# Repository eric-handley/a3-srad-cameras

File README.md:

# SRAD Cameras -  Operator's Manual

Please read the following document carefully as there are several important notes that could result in data loss or damage if ignored. After the rocket is recovered, please follow [Post-Flight Operations](#post-flight-operations).

Various tools for interacting with the camera boards have been provided in `./tools`. Each of these scripts can be passed `-h` as a flag to see the correct usage. Usage of these scripts is also detailed throughout this file. These scripts + this manual is largely written with the assumption that the user is on a reasonably mainstream Linux distro with common tools available. 

You will need a USB-C cable to pull files off of the camera (although the SD card should be imaged after flight as a precaution before doing this) and a USB<->UART adapter to send/receive camera commands/status.

Please send me a message if uncertain about anything or if issues arise!

## Table of Contents

- [Pre-Flight Checklist](#pre-flight-checklist)
    - [FPC Cable](#fpc-cable)
    - [Arducam Module](#arducam-module)
    - [SD Card](#sd-card)
    - [Operational Test](#operational-test)
    - [Before Launch](#before-launch)
- [Important Warnings & Info](#important-warnings--info)
- [Board Info](#board-info)
    - [Camera Status](#camera-status)
    - [Correct FPC Orientation](#correct-fpc-orientation)
    - [Arducam Ribbon connector](#arducam-ribbon-connector)
- [SD Card Operations](#sd-card-operations)
    - [SD Card Format](#sd-card-format)
- [Recovering Recordings](#recovering-recordings)
    - [Post-Flight Operations](#post-flight-operations)
    - [Pulling Recordings Directly](#pulling-recordings-directly)
- [Inspecting Recording Logs for Issues](#inspecting-recording-logs-for-issues)
    - [Common Errors & Causes](#common-errors--causes)
    - [`CAM2` Errata](#cam2-errata)

## Pre-Flight Checklist

This checklist is per-camera, e.g. each item should be checked on each camera module.

##### FPC Cable

- [ ] FPC is securely connected to both boards, without unneccesary strain, bends, or creases
- [ ] The FPC cable is oriented correctly (see [Correct FPC Orientation](#correct-fpc-orientation))
- [ ] The FPC cable is routed safely, away from power cables and PCBs (see [Important Warnings & Info](#important-warnings--info))
- [ ] If time permits, 3D print a cover for `CAM1` (Recovery Bay camera) to hold FPC away from board. Leave gap for airflow over SoC

##### Arducam Module

- [ ] The small black ribbon connector on the back of the module is in place (see [Arducam Ribbon connector](#arducam-ribbon-connector))
- [ ] The lens is oriented properly and lines up with its viewport (into Recovery/out of fuselage)

##### SD Card

- [ ] The SD card has been cleared using [./tools/wipe-sd-data](./tools/wipe-sd-data) (see [SD Card Operations](#sd-card-operations)) OR it has been verified over SSH using the `df` utility that the `/data` partition retains a significant portion of its capacity (preferably >50%)

##### Operational Test

- [ ] The camera board responds to `START`/`STOP` commands and correctly enters into and reports `STARTING`/`RECORDING`/`STOPPING`/`STOPPED` states based on commands from the Flight Computer/Ground Station
- [ ] After the above, the recording/logs can be pulled from the card properly using [./tools/pull-recording](./tools/pull-recording) (see [Recovering Recordings](#recovering-recordings))
- [ ] No non-benign error messages are reported in the various recording log files (see [Inspecting Recording Logs for Issues](#inspecting-recording-logs-for-issues))
- [ ] The resulting files can be properly combined using [./tools/mux](./tools/mux) and play without issues

##### Before Launch

- [ ] Power and UART lines are securely connected to the camera board and to Modular Power Supply/Flight Computer
- [ ] **IMPORTANT**: Slide switch on the camera board is in the `ON` position (closest to USB-C port)

## Important Warnings & Info

> [!WARNING]
> The SD cards already in the cameras have been correctly formatted as the SoC expects. You CANNOT clear or zero the entire SD card as this will wipe the OS!

> [!NOTE]
> The SD cards do not have a standard partition table as the SoC does not support this. This means that if you plug the SD card into your computer you will not see individual partitions/sizes/filesystem types, and it is not possible to pull files off the SD card this way. This is to be expected and is not an error. 

> [!WARNING]
> Do NOT plug in the USB-C cable while the main camera board is either powered through `JST1` or connected to the Modular Power Supply! Neither device has reverse-voltage protection for this scenario and the outcome of this is unpredictable and potentially damaging.

> [!WARNING]
> ALWAYS ensure that the camera reports a `STOPPED`/`0x0` state before switching it off or disconnecting it from the power supply. Sending `STOP` allows the camera to safely power down the SoC and unmount the SD card. While significant consideration has been given to preventing data loss during power-cut events, we do not want this to happen any more than necessary! The only time power should potentially be cut directly is during a non-nominal flight.

> [!NOTE]
> It is not possible to send commands that cause the camera to shut off in an unsafe way (unless the camera decides that this is necessary, e.g. in the case of SoC responses timing out). Sending `START` or `STOP` commands in any state will always be handled in a way that allows the SoC to unmount the SD card and shut down safely.

> [!CAUTION]
> Ensure the 1x22 FPC cable between the main camera board and the Arducam module is routed as far as possible from power cables and PCBs. The FPC should NEVER be pressed up against either the main camera PCB or the back of the Arducam PCB as this may cause the data sent through it to be corrupted. If this happens during flight, the recording will continue safely, but some non-zero number of frames will likely be lost.

## Board Info

### Camera Status

The status LED between the two JST connectors will blink 3 times on power-up to indicate that the STM32 has started. After this has completed, the LED has three possible states that indicate the overall status of the camera:

1. `STANDBY`: 5 seconds off, then 1 short blink
2. `RECORDING`: ~800 ms off, then ~800 ms on
    - Also present while the camera is `STOPPING`
    - The camera will stop `RECORDING` automatically after 30 minutes and shut down
3. `ERROR`: Rapidly blinking on/off every ~100 ms
    - This state may be temporary as the camera will try to recover automatically
    - If `ERROR` persists for more than a couple seconds, the best course of action is to send `STOP`, wait for `STOPPED`, then start the camera in `IDLE` and inspect the logs for the source of the issue
    - If no logs are produced by an `ERROR` state then the SoC never booted - this is caused by the PMIC on the PCB failing to start and the issue is likely related to voltage instability or unstable/poor ground connection. This is also a good first thing to check if errors occur

While the camera is in a transitional state between `STOPPED`/`STANDBY` and `RECORDING`, it will report either `STARTING` or `STOPPING`. This indicates that the SoC is in the process of booting or shutting down safely.

### Correct FPC Orientation

The correct orientation for the FPC ribbon cable is shown below. The cameras (as shipped) already have this orientation and ideally there is no need to disconnect the cable. However, this image can be referenced if necessary. The easiest way to tell that the cable orientation is correct is that the **blue rectangle on each end of the cable** should face: (a) toward the same side as the camera lens and (b) toward the top of the main board

To disconnect either side of the cable, you must first pull the two black tabs beside the cable out (shown in the image below). If you are pulling on the cable with any amount of force and it is not coming out, you have skipped this step! To put the cable back:

 - Make sure the black tabs are out
 - Insert the cable in the right orientation
 - GENTLY push the black tabs back into place, ideally while holding the other side of the connector 

### Arducam Ribbon connector

The back of the Arducam B0371 module has a small ribbon connector that carries various signals/voltages. This cable can easily become disconnected if the module is not handled carefully. Simply align the contacts and push the cable back into place.

## SD Card Operations

As noted in [Important Warnings & Info](#important-warnings--info), the MicroSD card used by the SoC has a non-standard partition setup to allow the SoC to properly read it. This means that you cannot a) mount the SD card as a regular drive with visible partitions or b) easily pull recordings off of the card by plugging it into your computer. Instead, follow [Recovering Recordings](#recovering-recordings).

### SD Card Format

The majority of the pre-written data on the MicroSD cards is the operating system used by the SoC; this should not be modified or overwritten under any circumstances. All recording data/logs are saved in the `/data` folder, which is a separate partition. All other partitions are always mounted read-only by the OS to avoid corruption. To safely clear the `/data` partition to clear up room for more recordings, you should do the following:

1. Save any recordings you want to keep (see [Pulling Recordings Directly](#pulling-recordings-directly))
2. Plug the SD card into your computer. Ensure it remains unmounted
3. Get the name of the device using `lsblk` (usually `mmcblk0`)
4. Use [./tools/wipe-sd-data](./tools/wipe-sd-data): `./wipe-sd-data <device-name>` to clear the data partition and safely reinitialize the ext4 filesystem it uses. The script will prompt you to confirm that the name of the device is correct before running

It is also possible to free up space by using [./tools/ssh-cam](./tools/ssh-cam) to SSH into a camera board over USB-C, then running `rm -rf /data/*`. However, this has the disadvantage of not fully reinitializing the filesystem used by the `/data` partition (thus potentially leaving corrupted filesystem info behind).

## Recovering Recordings

### Post-Flight Operations

Following recovery of the rocket, the following steps should be taken.

>[!WARNING]
> Do not mount the MicroSD cards and ensure that the computer used for this task will NOT attempt to automatically mount them! Some distros may be configured to do this when new disks are detected. It's unlikely this would cause issues but the risk should not be taken.

1. Switch off each camera and disconnect from Modular Power Supply
2. Remove SD cards from camera boards. Use the [./tools/image-sd](./tools/image-sd) utility to image both SD cards and save the raw contents to a file. Ideally label these `cam1.img` and `cam2.img` accordingly.
    - This is a backup precaution to make sure that (in the event of corruption) we have an exact copy of the disk before the OS attempts to repair it
    - Note: This will take quite a while and requires that your computer have at least 64GiB free
3. Once each camera's SD card has a `.img` file, you can attempt to pull the recordings using the boards directly (see next subsection). This is a significantly easier process than trying to extract them from the `.img` file manually.

### Pulling Recordings Directly

To put the cameras in a state where you can SSH into them or SCP files off of them, you must do the following:

1. Disconnect any other power sources from the board
2. **If post-flight**: Image the SD card as specified in the previous subsection
3. Plug the board into your computer using a USB-C cable
4. Connect a USB<->UART adapter to ground and to the `JST2`/1x2 Flight Computer connector OR the two header pins labled `FC` `RX/TX` on the back of the board.
5. Use [./tools/cam-send](./tools/cam-send) to send an `IDLE` command to the board: `./cam-send idle`. This boots the SoC without starting a recording. 
    - Note that in this mode, the `/data` partition is mounted read-only and therefore direct power cuts are not a concern (but getting in the habit of sending `./cam-send stop` before you disconnect the USB-C is still a good idea)
6. Use [./tools/pull-recording](./tools/pull-recording) to pull a single recording off of the SD card: `./pull-recording latest`
    - If you have not yet registered the camera's USB interface as an ethernet device, the script will prompt you to run `./tools/ssh-cam`, which should handle this automatically
    - `/data/latest` is a symlink to the most recently completed recording
    - Make sure if you are pulling `latest` multiple times that you rename the folder before pulling `latest` again - otherwise the contents will be overwritten.
7. Use [./tools/mux](./tools/mux) to combine the audio/video streams into a single `.mp4` file: `./mux <recording folder name>`
    - Requires `ffmpeg` and `mkvmerge` to be installed
    - Pretty please if you send this somewhere, do it in a way that doesn't destroy the bitrate/compress the video in a way that kills visual quality 🥲

Pulling any recording will also give you a `recordings.log` file. This file lists the folder names of all recordings made, e.g:

```
4aa29dfe5f15 <- saved in /data/4aa29dfe5f15
3362371f0132
7be752e098c8
75d7f5291437
7910d149b82b
becfb81627f5 <- most recent recording folder, /data/latest points here
```

## Inspecting Recording Logs for Issues

The following files should be created/updated by each recording (`START`/`STOP` cycle). If some are missing or duplicated (e.g. the same filename with a `.1`, `.2` suffix - this indicates a supervisor retry), something has gone wrong.

```sh
data
├── latest              # or uuid12 e.g. e051225d1440. `latest` is a symlink for most recent recording
│   ├── audio.log       # logs for `tinycap` which captures audio from ALSA
│   ├── audio.wav       # actual audio output file
│   ├── imu.csv         # timestamped imu data from STM32 along with temperature sensor readings
│   ├── kernel.log      # kernel logs for specific boot that captured this recording
│   ├── supervisor.log  # logs for supervisor script that starts other processes, e.g. video and 
│   │                   # audio recording. also handles logging imu data from STM32
│   ├── vicap.log       # logs from video capture process
│   ├── video.h265      # output h265 video
│   └── video.pts       # timestamps of every frame of h265. allows muxing to time frames 
│                       # correctly instead of distributing evenly according to FPS
├── recordings.log      # records the folder names of each new recording created
└── startup.log         # records an entry each time the supervisor script starts
```

#### Common Errors & Causes

> [!NOTE]
> Expect to see a fair amount of errors like the following:
> ```
>3,309,22874610,-;dwmmc_rockchip ffaa0000.mmc: Card stuck in wrong state! card_busy_detect status: 0x0 caller=mmc_blk_mq_complete_prev_req.part.4+0x89/0xe4
>3,310,22874669,-;MMCDBG mmcblk1: recovery dir=WRITE pos=34940552 cmd_err=0 data_err=0 stop_err=0 status=0xd00 send_status_err=0
>6,311,22889830,-;mmc_host mmc1: Bus speed (slot 0) = 400000Hz (slot req 400000Hz, actual 400000HZ div = 0)
>```
> These are benign and are related to issues with Rockchip's MMC drivers. No data is lost by these, they might just slow down boot times slightly

> ___
> #### Error Message:
>
> None, no new log files were created or most recent recording looks to have exited correctly
>
> #### Behaviour:
> 
> LED goes directly from `STANDBY` state to `ERROR` state and stays there
>
> #### Cause:
>
> Unstable voltage or ground connection. PMIC was never able to start properly so SoC did not boot
> 
> ---

> ___
> #### Error Message:
>
> kernel.log:
> ```
>Unexpected sensor id(xxxx)
>```
>
> #### Behaviour:
> 
> Recording fails to start and no `video.h265` file is present, some log files are missing or supervisor.log reports an error exit value for `uvr-vicap.c`
>
> #### Cause:
>
> Sensor not connected properly; FPC cable either disconnected or oriented wrong. Arducam ribbon cable may be dislodged. 
> 
> ---

> ___
> #### Error Message:
>
> kernel.log:
> ```
> 3,443,486143421,-;mipi-csi2-hw ERR1:0x11000110 (fs/fe mis,vc: 0) (f_seq,vc: 0) (crc,vc: 0) (ecc2) 
> 3,444,486151886,-;mipi-csi2-hw ERR1:0x10000000 (ecc2) 
> 3,447,486168584,-;mipi-csi2-hw ERR2:0x100 (ecc,vc: 0) 
> 3,448,486191410,-;mipi-csi2-hw ERR1:0x10000100 (f_seq,vc: 0) (ecc2) 
> ```
>
> (or similar)
>
> #### Behaviour:
> 
> All log files and output files are present. `vicap.log` may have a large number of `SOF` errors (a small number is normal) or report an FPS different from 60fps at exit
>
> #### Cause:
>
> MIPI errors caused by FPC cable being too close to a PCB or voltage source
> 
> ---

> ___
> #### Error Message:
>
> supervisor.log:
> ```
> [2024-01-01T00:02:19.500143] csv write failed after 11272 rows ([Errno 28] No space left on device), reopening
> ```
>
> #### Behaviour:
> 
> No new recording created; pulled recording looks the same as last one
>
> #### Cause:
>
> `/data` partition is full
> 
> ---

#### `CAM2` Errata

Two things are broken (marginally functional) on `CAM2` (horizon camera) due to questionable soldering:

1. SoC internal temperature sensor
2. Microphone

This means that logs will display `SoC temp nanC` and the audio file will just be noise/*very* faint. `CAM2` may also have kernel logs related to `implausible reading 180C`; these are benign and don't reflect actual temperature readings.

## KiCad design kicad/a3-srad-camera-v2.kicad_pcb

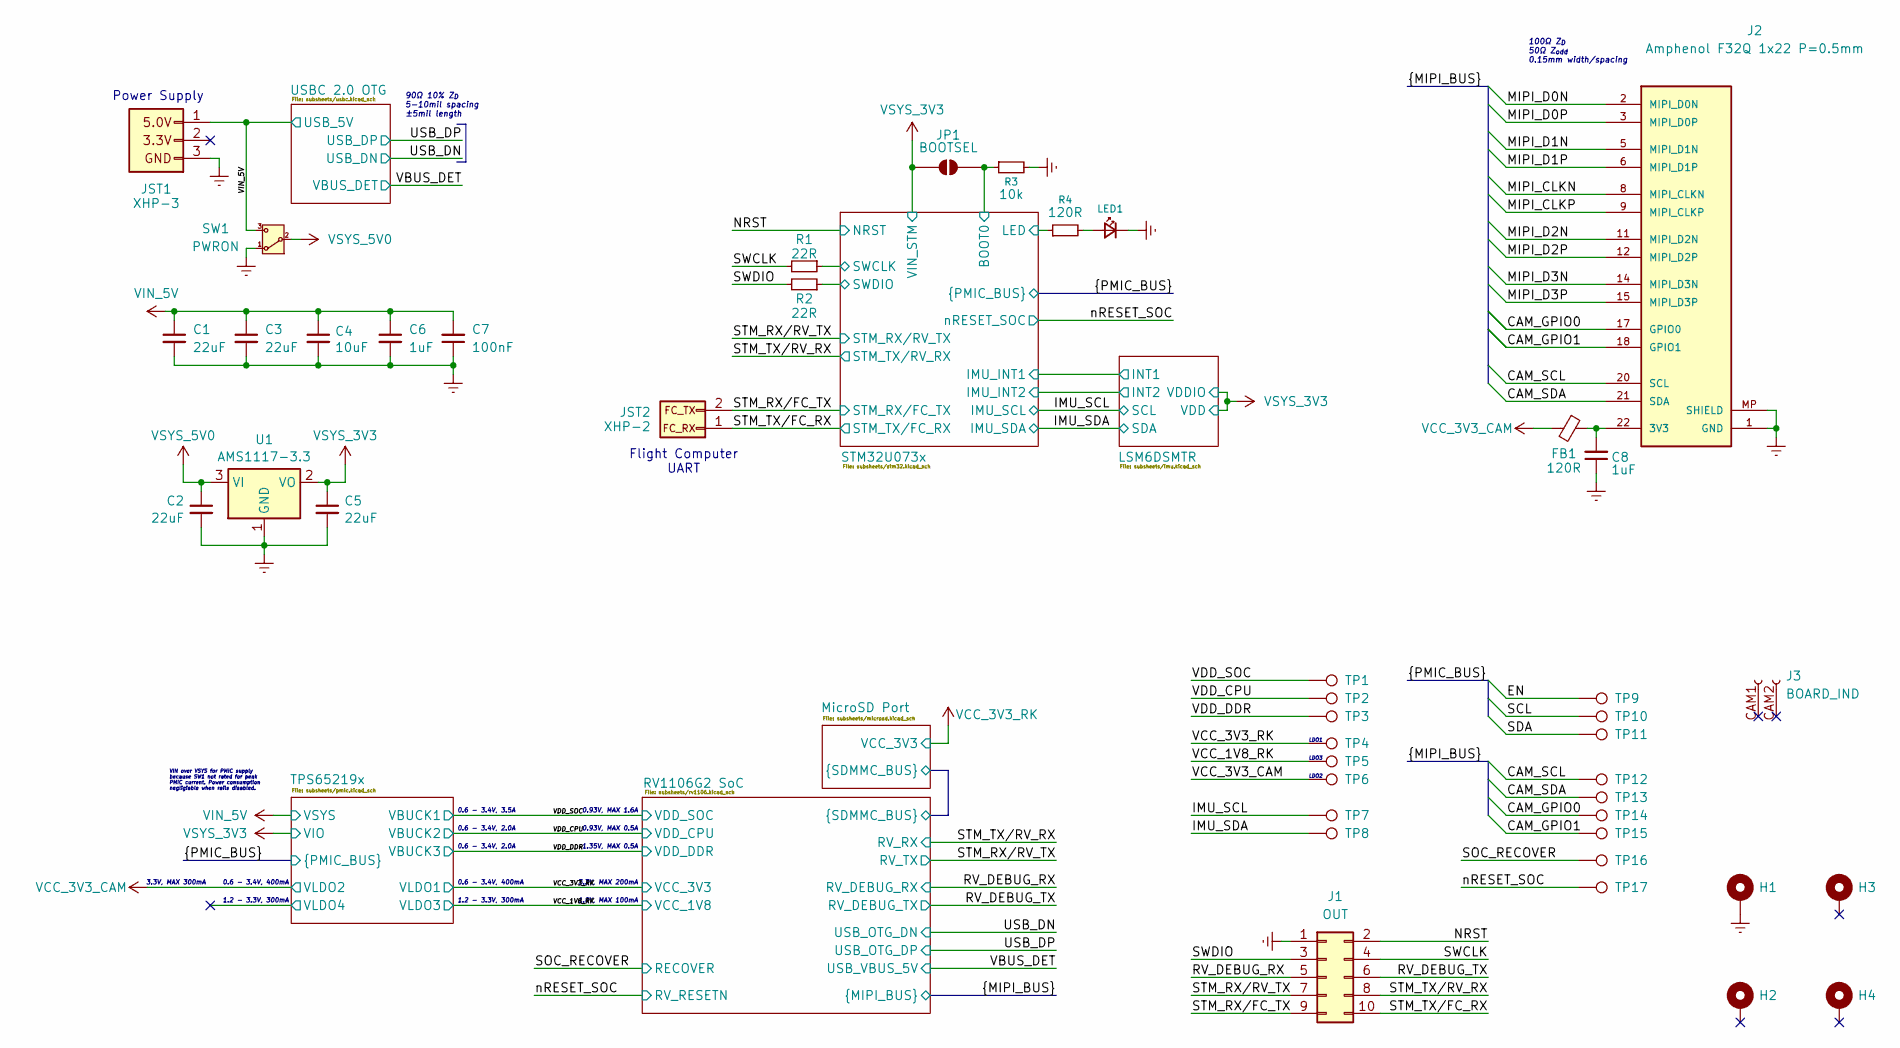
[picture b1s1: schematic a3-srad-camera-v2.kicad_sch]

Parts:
C1, C3: 22uF; C_1206_3216Metric; LCSC PART NAME C15850
C2, C5: 22uF; C_1206_3216Metric
C4: 10uF; C_0805_2012Metric
C6: 1uF; C_0603_1608Metric
C7: 100nF; C_0402_1005Metric
C8: 1uF; C_0603_1608Metric; LCSC PART NAME C15849
FB1: 120R; R_0603_1608Metric; LCSC PART NAME C14709
H1, H2, H3, H4: MntHole; 4-40_MountingHole
J1: OUT; PinHeader_2x05_P2.54mm_Vertical
J2: Amphenol F32Q 1x22 P=0.5mm; Amphenol_F32Q-1A7x1-11022_1x22-1MP_P0.5mm_Horizontal; PARTREV D
J3: BOARD_IND; Board_Indicator
JP1: BOOTSEL; SolderJumper-2_P1.3mm_Open_Pad1.0x1.5mm
JST1: XHP-3; JST_XH_B3B-XH-A_1x03_P2.50mm_Vertical; LCSC PART NAME C144402
JST2: XHP-2; JST_XH_B2B-XH-A_1x02_P2.50mm_Vertical; LCSC PART NAME C144401
LED1: LED_0805_2012Metric; LCSC PART NAME C2297
R1, R2: 22R; R_0402_1005Metric; LCSC PART NAME C25092
R3: 10k; R_0603_1608Metric; LCSC PART NAME C112291
R4: 120R; R_0402_1005Metric; LCSC PART NAME C112291
SW1: PWRON; SW_Slide_SPDT_Angled_CK_OS102011MA1Q; LCSC PART NAME C221841
TP1, TP2, TP3, TP4, TP5, TP6, TP7, TP8, TP9, TP10, TP11, TP12, TP13, TP14, TP15, TP16, TP17: TestPoint; TestPoint_Pad_D2.0mm_Small_Courtyard
U1: AMS1117-3.3; SOT-223-3_TabPin2

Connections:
/CAM_GPIO0: J2.17 (GPIO0), TP14.1 (1_1); also elsewhere on the board
/CAM_GPIO1: J2.18 (GPIO1), TP15.1 (1_1); also elsewhere on the board
/CAM_SCL: J2.20 (SCL), TP12.1 (1_1); also elsewhere on the board
/CAM_SDA: J2.21 (SDA), TP13.1 (1_1); also elsewhere on the board
/EN: TP9.1 (1_1); also elsewhere on the board
/IMU_SCL: TP7.1 (1_1); also elsewhere on the board
/IMU_SDA: TP8.1 (1_1); also elsewhere on the board
/MIPI_CLKN: J2.8 (MIPI_CLKN); also elsewhere on the board
/MIPI_CLKP: J2.9 (MIPI_CLKP); also elsewhere on the board
/MIPI_D0N: J2.2 (MIPI_D0N); also elsewhere on the board
/MIPI_D0P: J2.3 (MIPI_D0P); also elsewhere on the board
/MIPI_D1N: J2.5 (MIPI_D1N); also elsewhere on the board
/MIPI_D1P: J2.6 (MIPI_D1P); also elsewhere on the board
/MIPI_D2N: J2.11 (MIPI_D2N); also elsewhere on the board
/MIPI_D2P: J2.12 (MIPI_D2P); also elsewhere on the board
/MIPI_D3N: J2.14 (MIPI_D3N); also elsewhere on the board
/MIPI_D3P: J2.15 (MIPI_D3P); also elsewhere on the board
/NRST: J1.2; also elsewhere on the board
/RV_DEBUG_RX: J1.5; also elsewhere on the board
/RV_DEBUG_TX: J1.6; also elsewhere on the board
/SCL: TP10.1 (1_1); also elsewhere on the board
/SDA: TP11.1 (1_1); also elsewhere on the board
/SOC_RECOVER: TP16.1 (1_1); also elsewhere on the board
/STM32U073x/BOOT0: JP1.2 (B), R3.1; also elsewhere on the board
/STM32U073x/LED: R4.1; also elsewhere on the board
/STM32U073x/SWCLK: R1.1; also elsewhere on the board
/STM32U073x/SWDIO: R2.1; also elsewhere on the board
/STM_RX/FC_TX: J1.9, JST2.2; also elsewhere on the board
/STM_RX/RV_TX: J1.7; also elsewhere on the board
/STM_TX/FC_RX: J1.10, JST2.1; also elsewhere on the board
/STM_TX/RV_RX: J1.8; also elsewhere on the board
/SWCLK: J1.4, R1.2
/SWDIO: J1.3, R2.2
/VCC_1V8_RK: TP5.1 (1_1); also elsewhere on the board
/VDD_CPU: TP2.1 (1_1); also elsewhere on the board
/VDD_DDR: TP3.1 (1_1); also elsewhere on the board
/VDD_SOC: TP1.1 (1_1); also elsewhere on the board
/nRESET_SOC: TP17.1 (1_1); also elsewhere on the board
GND: C1.2, C2.2, C3.2, C4.2, C5.2, C6.2, C7.1, C8.1, H1.1 (MP_1), J1.1, J2.1 (GND), J2.4, J2.7, J2.10, J2.13, J2.16, J2.19, J2.MP (SHIELD), JST1.3, LED1.1 (K), R3.2, SW1.1 (A), U1.1 (GND); also elsewhere on the board
unnamed: C8.2, FB1.1, J2.22 (3V3)
unnamed: LED1.2 (A), R4.2
VCC_3V3_CAM: FB1.2, TP6.1 (1_1); also elsewhere on the board
VCC_3V3_RK: TP4.1 (1_1); also elsewhere on the board
VIN_5V: C1.1, C3.1, C4.1, C6.1, C7.2, JST1.1, SW1.3 (C); also elsewhere on the board
VSYS_3V3: C5.1, JP1.1 (A), U1.2 (VO); also elsewhere on the board
VSYS_5V0: C2.1, SW1.2 (B), U1.3 (VI)

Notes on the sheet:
3.3V, MAX 200mA
3.3V, MAX 300mA
VIN over VSYS for PMIC supply because SW1 not rated for peak PMIC current. Power consumption negligiable when rails disabled.
1.8V, MAX 100mA
1.2 - 3.3V, 300mA
0.93V, MAX 0.5A
0.6 - 3.4V, 2.0A
0.6 - 3.4V, 400mA
Power Supply
90Ω 10% Z_{D} 5-10mil spacing ±5mil length
LDO2
LDO1
100Ω Z_{D} 50Ω Z_{odd} 0.15mm width/spacing
0.93V, MAX 1.6A
LDO3
Flight Computer UART
1.35V, MAX 0.5A
0.6 - 3.4V, 3.5A

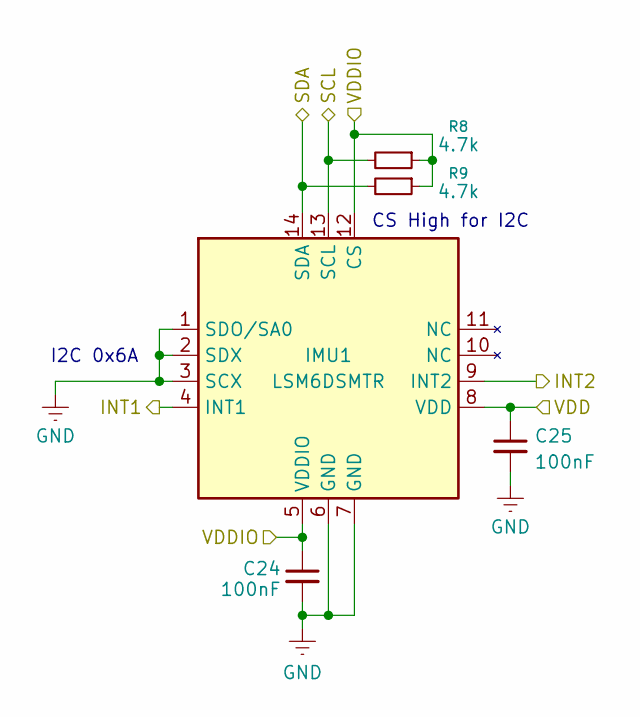
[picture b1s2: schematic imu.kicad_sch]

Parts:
C24, C25: 100nF; C_0402_1005Metric; LCSC PART NAME C1525
IMU1: LSM6DSMTR; LGA-14_3x2.5mm_P0.5mm_LayoutBorder3x4y; LCSC PART NAME C126672
R8, R9: 4.7k; R_0402_1005Metric; LCSC PART NAME C25900

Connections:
/IMU_SCL: IMU1.13 (SCL), R8.2; also elsewhere on the board
/IMU_SDA: IMU1.14 (SDA), R9.2; also elsewhere on the board
/LSM6DSMTR/INT1: IMU1.4 (INT1); also elsewhere on the board
/LSM6DSMTR/INT2: IMU1.9 (INT2); also elsewhere on the board
GND: C24.2, C25.2, IMU1.1 (SDO/SA0), IMU1.2 (SDX), IMU1.3 (SCX), IMU1.6 (GND), IMU1.7 (GND); also elsewhere on the board
VSYS_3V3: C24.1, C25.1, IMU1.5 (VDDIO), IMU1.8 (VDD), IMU1.12 (CS), R8.1, R9.1; also elsewhere on the board

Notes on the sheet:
I2C 0x6A
CS High for I2C

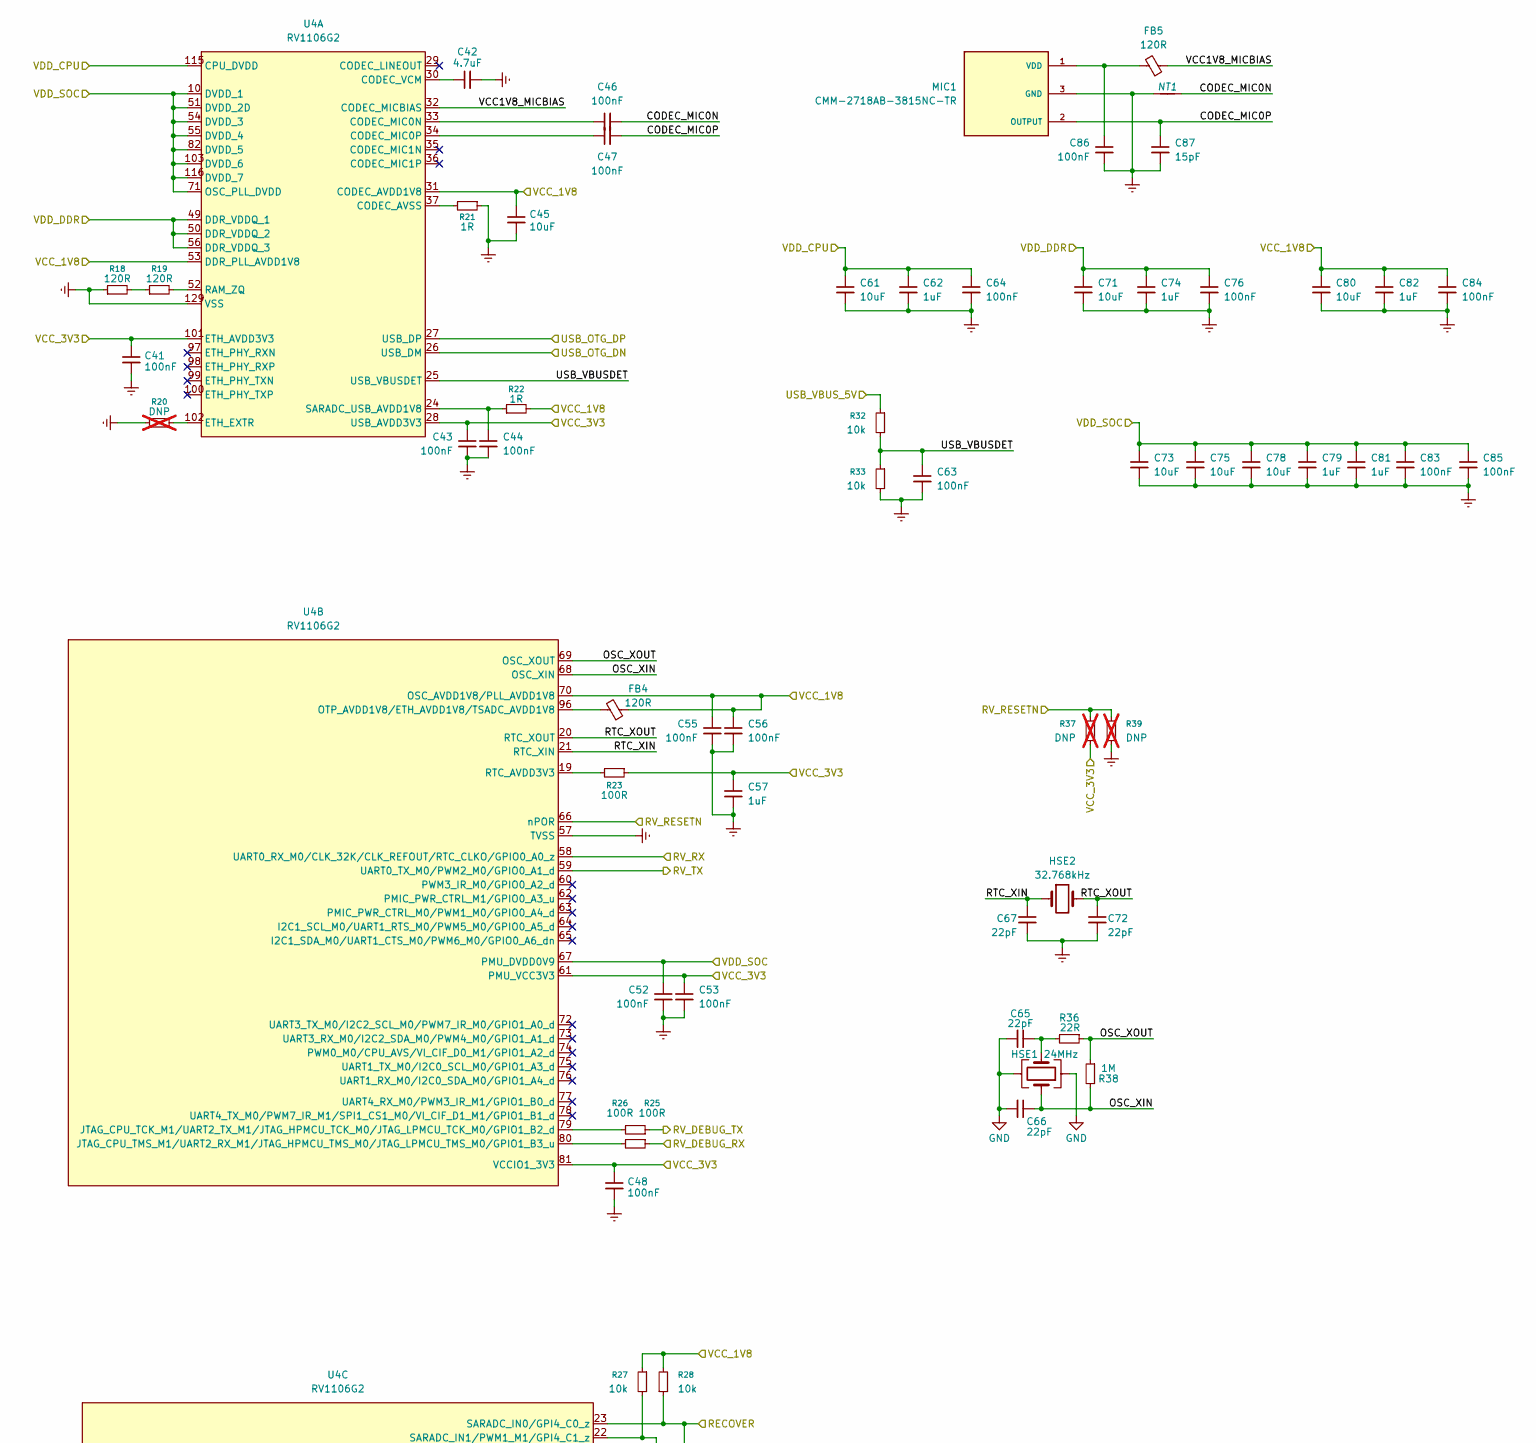
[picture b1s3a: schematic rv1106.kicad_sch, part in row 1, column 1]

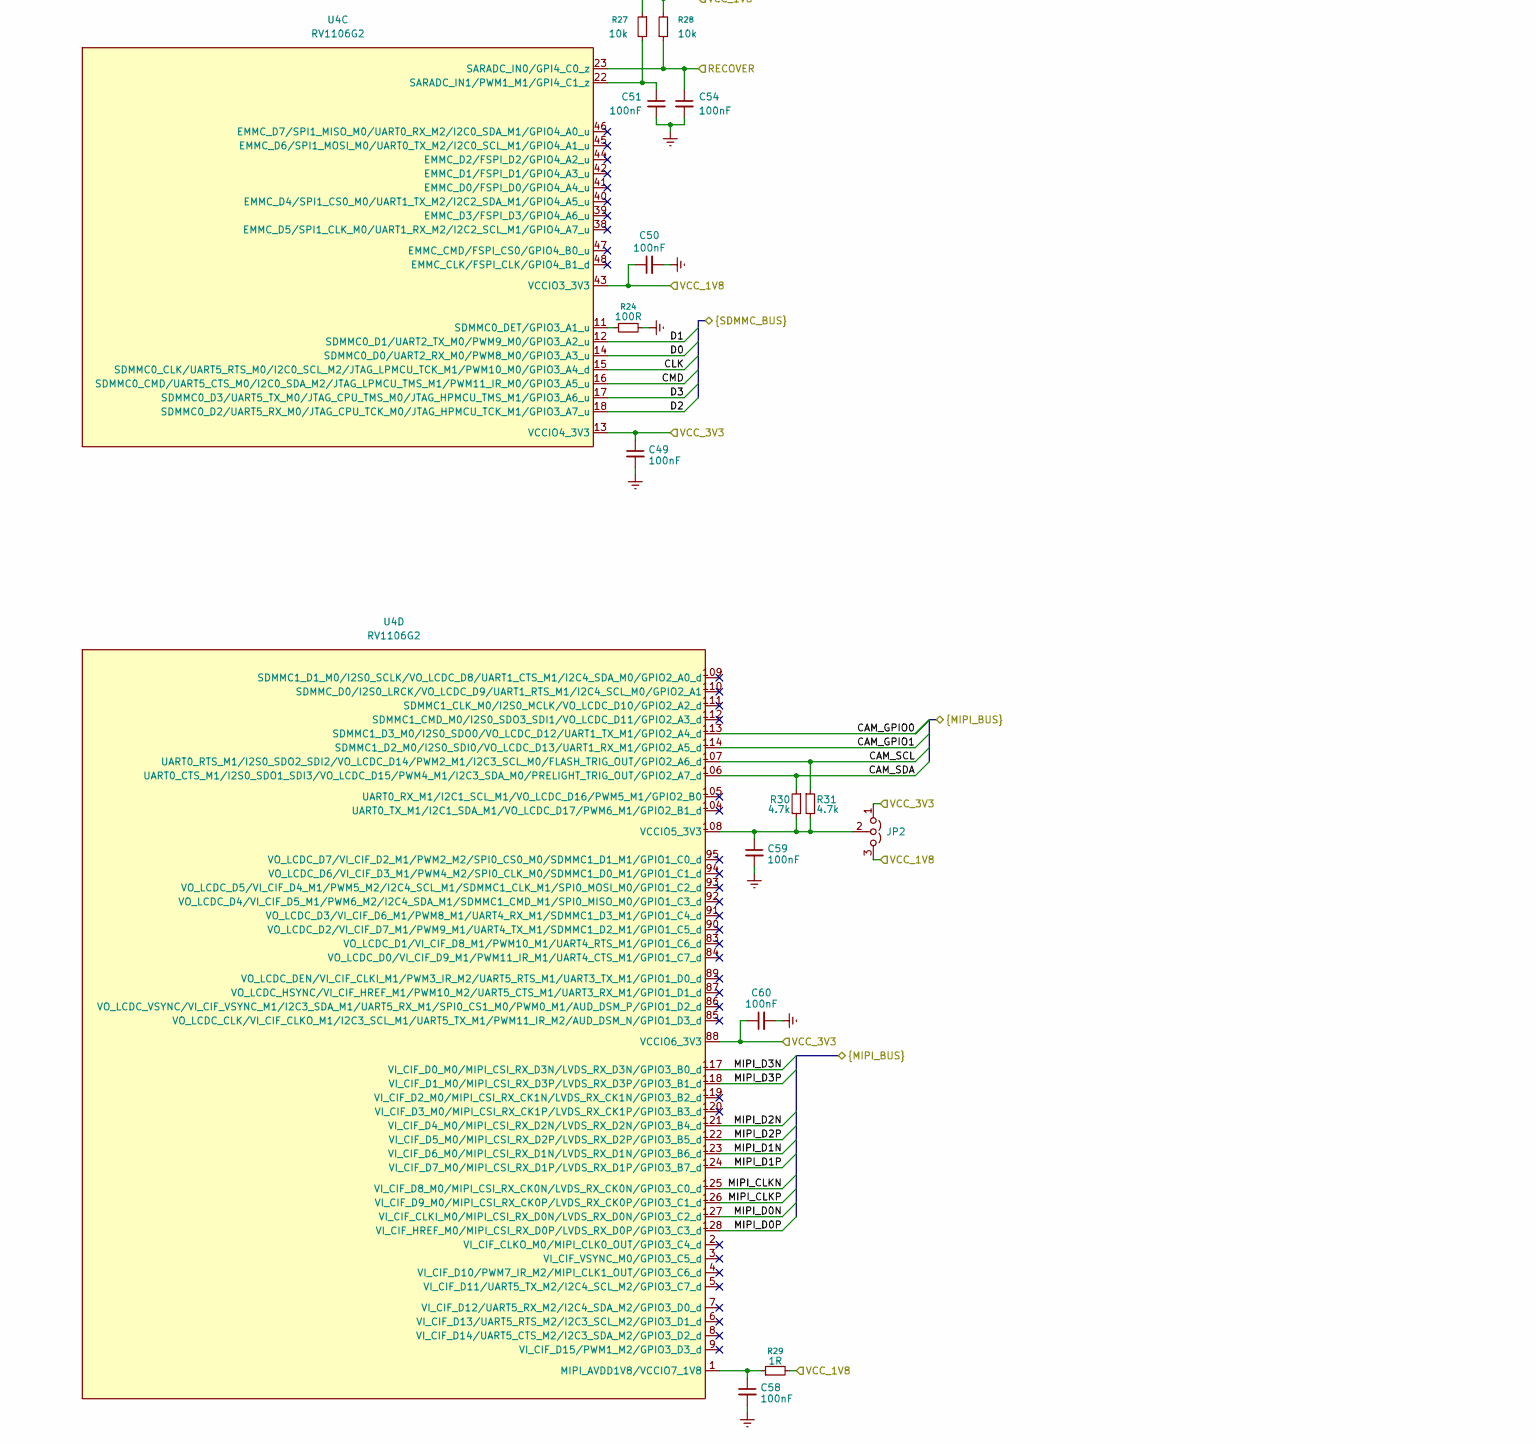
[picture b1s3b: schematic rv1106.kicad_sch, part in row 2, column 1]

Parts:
C41, C43, C44, C46, C47, C48, C49, C50, C51, C52, C53, C54, C55, C56, C58, C59, C60, C63, C64, C76, C83, C84, C85, C86: 100nF; C_0402_1005Metric
C42: 4.7uF; C_0805_2012Metric
C45, C61, C71, C73, C75, C78, C80: 10uF; C_0805_2012Metric
C57, C62, C74, C79, C81, C82: 1uF; C_0603_1608Metric
C65, C66, C67, C72: 22pF; C_0402_1005Metric; LCSC PART NAME C1555
C87: 15pF; C_0402_1005Metric
FB4, FB5: 120R; R_0603_1608Metric
HSE1: 24MHz; Crystal_SMD_2016-4Pin_2.0x1.6mm; LCSC PART NAME C725986
HSE2: 32.768kHz; Crystal_SMD_3215-2Pin_3.2x1.5mm; LCSC PART NAME C32346
JP2: Jumper_3_Open; SolderJumper-3_P1.3mm_Open_Pad1.0x1.5mm_NumberLabels
MIC1: CMM-2718AB-3815NC-TR; MIC_CMM-2718AB-3815NC-TR; PARTREV 1.02
NT1: NetTie_2
R18, R19: 120R; R_0402_1005Metric
R20, R37, R39: DNP; R_0402_1005Metric; not fitted
R21, R22, R29: 1R; R_0402_1005Metric
R23, R24, R25, R26: 100R; R_0402_1005Metric
R27, R28, R32, R33: 10k; R_0603_1608Metric; LCSC PART NAME C112291
R30, R31: 4.7k; R_0402_1005Metric; LCSC PART NAME C25092
R36: 22R; R_0402_1005Metric; LCSC PART NAME C25092
R38: 1M; R_0402_1005Metric; LCSC PART NAME C26083
U4: RV1106G2; QFN-128_L12.3-W12.3-P0.35-TL-EP7.0-1; MPN RV1106G2; LCSC Part C5272606

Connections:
/CAM_GPIO0: U4.113 (SDMMC1_D3_M0/I2S0_SDO0/VO_LCDC_D12/UART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); also elsewhere on the board
/CAM_GPIO1: U4.114 (SDMMC1_D2_M0/I2S0_SDI0/VO_LCDC_D13/UART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); also elsewhere on the board
/CAM_SCL: R31.1, U4.107 (UART0_RTS_M1/I2S0_SDO2_SDI2/VO_LCDC_D14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); also elsewhere on the board
/CAM_SDA: R30.1, U4.106 (UART0_CTS_M1/I2S0_SDO1_SDI3/VO_LCDC_D15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); also elsewhere on the board
/MIPI_CLKN: U4.125 (VI_CIF_D8_M0/MIPI_CSI_RX_CK0N/LVDS_RX_C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); also elsewhere on the board
/MIPI_CLKP: U4.126 (VI_CIF_D9_M0/MIPI_CSI_RX_CK0P/LVDS_RX_C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); also elsewhere on the board
/MIPI_D0N: U4.127 (VI_CIF_CLKI_M0/MIPI_CSI_RX_D0N/LVDS_RX_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); also elsewhere on the board
/MIPI_D0P: U4.128 (VI_CIF_HREF_M0/MIPI_CSI_RX_D0P/LVDS_RX_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); also elsewhere on the board
/MIPI_D1N: U4.123 (VI_CIF_D6_M0/MIPI_CSI_RX_D1N/LVDS_RX_D1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); also elsewhere on the board
/MIPI_D1P: U4.124 (VI_CIF_D7_M0/MIPI_CSI_RX_D1P/LVDS_RX_D1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); also elsewhere on the board
/MIPI_D2N: U4.121 (VI_CIF_D4_M0/MIPI_CSI_RX_D2N/LVDS_RX_D2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); also elsewhere on the board
/MIPI_D2P: U4.122 (VI_CIF_D5_M0/MIPI_CSI_RX_D2P/LVDS_RX_D2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); also elsewhere on the board
/MIPI_D3N: U4.117 (VI_CIF_D0_M0/MIPI_CSI_RX_D3N/LVDS_RX_D3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); also elsewhere on the board
/MIPI_D3P: U4.118 (VI_CIF_D1_M0/MIPI_CSI_RX_D3P/LVDS_RX_D3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); also elsewhere on the board
/MicroSD Port/CLK: U4.15 (SDMMC0_CLK/UART5_RTS_M0/I2C0_SCL_M2/JTA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); also elsewhere on the board
/MicroSD Port/CMD: U4.16 (SDMMC0_CMD/UART5_CTS_M0/I2C0_SDA_M2/JTA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); also elsewhere on the board
/MicroSD Port/D0: U4.14 (SDMMC0_D0/UART2_RX_M0/PWM8_M0/GPIO3_A3_u); also elsewhere on the board
/MicroSD Port/D1: U4.12 (SDMMC0_D1/UART2_TX_M0/PWM9_M0/GPIO3_A2_u); also elsewhere on the board
/MicroSD Port/D2: U4.18 (SDMMC0_D2/UART5_RX_M0/JTAG_CPU_TCK_M0/J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); also elsewhere on the board
/MicroSD Port/D3: U4.17 (SDMMC0_D3/UART5_TX_M0/JTAG_CPU_TMS_M0/J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); also elsewhere on the board
/RV1106G2 SoC/CODEC_MIC0N: C46.2, NT1.2
/RV1106G2 SoC/CODEC_MIC0P: C47.2, C87.1, MIC1.2 (OUTPUT)
/RV1106G2 SoC/OSC_XIN: C66.1, HSE1.1, R38.2, U4.68 (OSC_XIN)
/RV1106G2 SoC/OSC_XOUT: R36.1, R38.1, U4.69 (OSC_XOUT)
/RV1106G2 SoC/RTC_XIN: C67.1, HSE2.1, U4.21 (RTC_XIN)
/RV1106G2 SoC/RTC_XOUT: C72.1, HSE2.2, U4.20 (RTC_XOUT)
/RV1106G2 SoC/USB_VBUSDET: C63.1, R32.2, R33.1, U4.25 (USB_VBUSDET)
/RV1106G2 SoC/VCC1V8_MICBIAS: FB5.1, U4.32 (CODEC_MICBIAS)
/RV_DEBUG_RX: R26.1; also elsewhere on the board
/RV_DEBUG_TX: R25.1; also elsewhere on the board
/SOC_RECOVER: C54.1, R28.1, U4.23 (SARADC_IN0/GPI4_C0_z); also elsewhere on the board
/STM_RX/RV_TX: U4.59 (UART0_TX_M0/PWM2_M0/GPIO0_A1_d); also elsewhere on the board
/STM_TX/RV_RX: U4.58 (UART0_RX_M0/CLK_32K/CLK_REFOUT/RTC_CLKO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); also elsewhere on the board
/USB_DN: U4.26 (USB_DM); also elsewhere on the board
/USB_DP: U4.27 (USB_DP); also elsewhere on the board
/VCC_1V8_RK: C45.1, C50.1, C55.1, C56.1, C80.1, C82.1, C84.1, FB4.1, JP2.3 (B), R22.2, R27.1, R28.2, R29.2, U4.31 (CODEC_AVDD1V8), U4.43 (VCCIO3_3V3), U4.53 (DDR_PLL_AVDD1V8), U4.70 (OSC_AVDD1V8/PLL_AVDD1V8); also elsewhere on the board
/VDD_CPU: C61.1, C62.1, C64.1, U4.115 (CPU_DVDD); also elsewhere on the board
/VDD_DDR: C71.1, C74.1, C76.1, U4.49 (DDR_VDDQ_1), U4.50 (DDR_VDDQ_2), U4.56 (DDR_VDDQ_3); also elsewhere on the board
/VDD_SOC: C52.1, C73.1, C75.1, C78.1, C79.1, C81.1, C83.1, C85.1, U4.10 (DVDD_1), U4.51 (DVDD_2D), U4.54 (DVDD_3), U4.55 (DVDD_4), U4.67 (PMU_DVDD0V9), U4.71 (OSC_PLL_DVDD), U4.82 (DVDD_5), U4.103 (DVDD_6), U4.116 (DVDD_7); also elsewhere on the board
/nRESET_SOC: R37.2, R39.2, U4.66 (nPOR); also elsewhere on the board
GND: C41.2, C42.2, C43.2, C44.2, C45.2, C48.2, C49.2, C50.2, C51.2, C52.2, C53.2, C54.2, C55.2, C56.2, C57.2, C58.2, C59.2, C60.2, C61.2, C62.2, C63.2, C64.2, C65.2, C66.2, C67.2, C71.2, C72.2, C73.2, C74.2, C75.2, C76.2, C78.2, C79.2, C80.2, C81.2, C82.2, C83.2, C84.2, C85.2, C86.2, C87.2, HSE1.2, HSE1.4, MIC1.3 (GND), NT1.1, R18.1, R20.1, R21.1, R24.2, R33.2, R39.1, U4.57 (TVSS), U4.129 (VSS); also elsewhere on the board
unnamed: C65.1, HSE1.3, R36.2
unnamed: C59.1, JP2.2 (C), R30.2, R31.2, U4.108 (VCCIO5_3V3)
unnamed: C86.1, FB5.2, MIC1.1 (VDD)
unnamed: R18.2, R19.1
unnamed: R21.2, U4.37 (CODEC_AVSS)
unnamed: C46.1, U4.33 (CODEC_MIC0N)
unnamed: C47.1, U4.34 (CODEC_MIC0P)
unnamed: C42.1, U4.30 (CODEC_VCM)
unnamed: R20.2, U4.102 (ETH_EXTR)
unnamed: R19.2, U4.52 (RAM_ZQ)
unnamed: C44.1, R22.1, U4.24 (SARADC_USB_AVDD1V8)
unnamed: R25.2, U4.79 (JTAG_CPU_TCK_M1/UART2_TX_M1/JTAG_HPMCU_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)
unnamed: R26.2, U4.80 (JTAG_CPU_TMS_M1/UART2_RX_M1/JTAG_HPMCU_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)
unnamed: FB4.2, U4.96 (OTP_AVDD1V8/ETH_AVDD1V8/TSADC_AVDD1V8)
unnamed: R23.2, U4.19 (RTC_AVDD3V3)
unnamed: C51.1, R27.2, U4.22 (SARADC_IN1/PWM1_M1/GPI4_C1_z)
unnamed: R24.1, U4.11 (SDMMC0_DET/GPIO3_A1_u)
unnamed: C58.1, R29.1, U4.1 (MIPI_AVDD1V8/VCCIO7_1V8)
VBUS_5V: R32.1; also elsewhere on the board
VCC_3V3_RK: C41.1, C43.1, C48.1, C49.1, C53.1, C57.1, C60.1, JP2.1 (A), R23.1, R37.1, U4.13 (VCCIO4_3V3), U4.28 (USB_AVDD3V3), U4.61 (PMU_VCC3V3), U4.81 (VCCIO1_3V3), U4.88 (VCCIO6_3V3), U4.101 (ETH_AVDD3V3); also elsewhere on the board

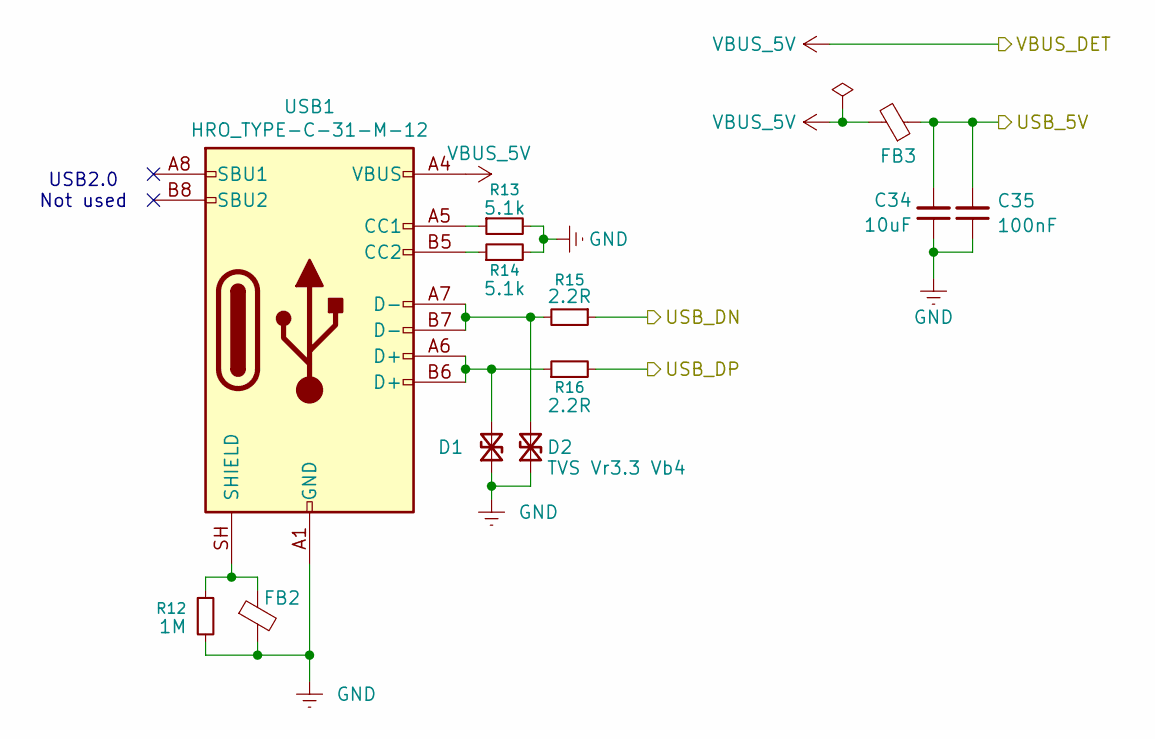
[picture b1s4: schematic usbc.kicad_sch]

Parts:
C34: 10uF; C_0805_2012Metric; LCSC PART NAME C15850
C35: 100nF; C_0402_1005Metric; LCSC PART NAME C1525
D1, D2: TVS Vr3.3 Vb4; D_SOD-323; LCSC PART NAME C19077496
FB2, FB3: 120R; R_0603_1608Metric; LCSC PART NAME C14709
R12: 1M; R_0402_1005Metric; LCSC PART NAME C26083
R13, R14: 5.1k; R_0402_1005Metric; LCSC PART NAME C25905
R15, R16: 2.2R; R_0402_1005Metric; LCSC PART NAME C25092
USB1: HRO_TYPE-C-31-M-12; USB_C_Receptacle_HRO_TYPE-C-31-M-12; LCSC PART NAME C165948

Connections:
/USB_DN: R15.1; also elsewhere on the board
/USB_DP: R16.2; also elsewhere on the board
GND: C34.1, C35.1, D1.1 (A1), D2.1 (A1), FB2.2, R12.2, R13.2, R14.2, USB1.A1 (GND), USB1.A12 (GND), USB1.B1 (GND), USB1.B12 (GND); also elsewhere on the board
unnamed: D1.2 (A2), R16.1, USB1.A6 (D+), USB1.B6 (D+)
unnamed: D2.2 (A2), R15.2, USB1.A7 (D-), USB1.B7 (D-)
unnamed: R13.1, USB1.A5 (CC1)
unnamed: R14.1, USB1.B5 (CC2)
unnamed: FB2.1, R12.1, USB1.SH (SHIELD)
VBUS_5V: FB3.2, USB1.A4 (VBUS), USB1.A9 (VBUS), USB1.B4 (VBUS), USB1.B9 (VBUS); also elsewhere on the board
VIN_5V: C34.2, C35.2, FB3.1; also elsewhere on the board

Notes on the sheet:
USB2.0 Not used

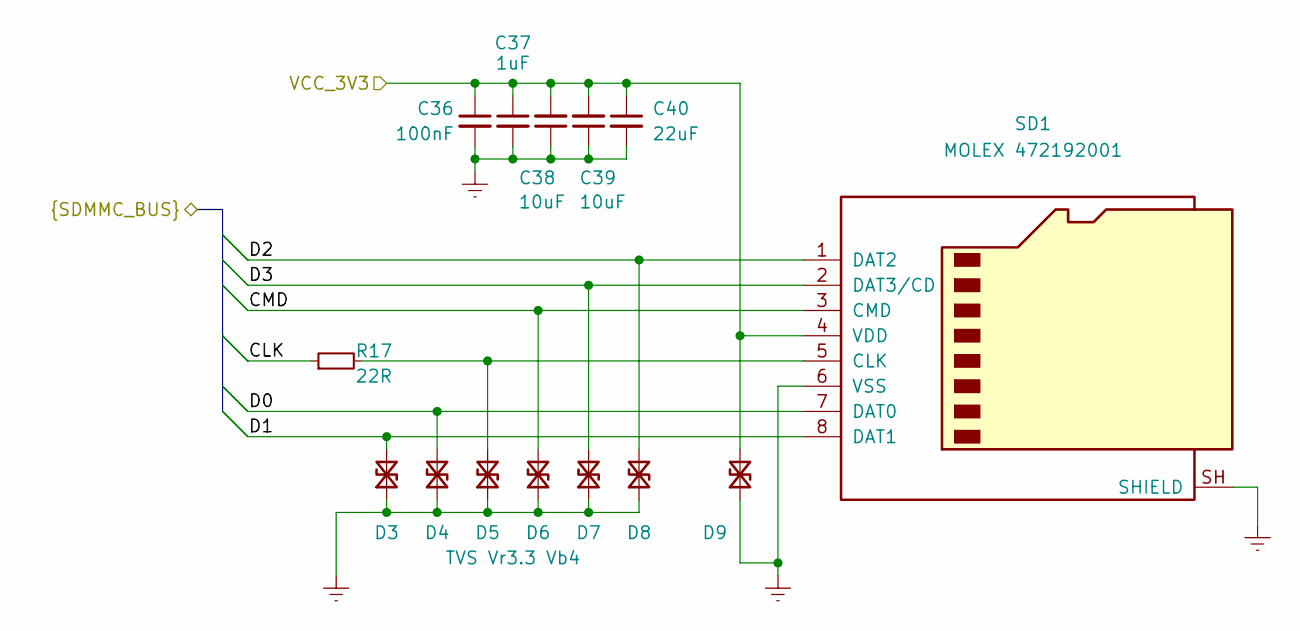
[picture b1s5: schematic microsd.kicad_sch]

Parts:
C36: 100nF; C_0402_1005Metric; LCSC PART NAME C1525
C37: 1uF; C_0603_1608Metric; LCSC PART NAME C15849
C38, C39: 10uF; C_0805_2012Metric; LCSC PART NAME C15850
C40: 22uF; C_1206_3216Metric; LCSC PART NAME C15850
D3, D4, D5, D6, D7, D8, D9: TVS Vr3.3 Vb4; D_SOD-323; LCSC PART NAME C19077496
R17: 22R; R_0402_1005Metric; LCSC PART NAME C25092
SD1: MOLEX 472192001; microSD_HC_Molex_47219-2001; LCSC PART NAME C164170

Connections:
/MicroSD Port/CLK: R17.1; also elsewhere on the board
/MicroSD Port/CMD: D6.2 (A2), SD1.3 (CMD); also elsewhere on the board
/MicroSD Port/D0: D4.2 (A2), SD1.7 (DAT0); also elsewhere on the board
/MicroSD Port/D1: D3.2 (A2), SD1.8 (DAT1); also elsewhere on the board
/MicroSD Port/D2: D8.2 (A2), SD1.1 (DAT2); also elsewhere on the board
/MicroSD Port/D3: D7.2 (A2), SD1.2 (DAT3/CD); also elsewhere on the board
GND: C36.2, C37.2, C38.1, C39.1, C40.2, D3.1 (A1), D4.1 (A1), D5.1 (A1), D6.1 (A1), D7.1 (A1), D8.1 (A1), D9.1 (A1), SD1.6 (VSS), SD1.SH (SHIELD); also elsewhere on the board
unnamed: D5.2 (A2), R17.2, SD1.5 (CLK)
VCC_3V3_RK: C36.1, C37.1, C38.2, C39.2, C40.1, D9.2 (A2), SD1.4 (VDD); also elsewhere on the board

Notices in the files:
stm32/Core/Src/main.c:
Copyright (c) 2026 STMicroelectronics.
All rights reserved.
This software is licensed under terms that can be found in the LICENSE file
